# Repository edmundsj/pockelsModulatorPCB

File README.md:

# pockelsModulatorPCB
Printed Circuit Board (PCB) for pockels modulator chip

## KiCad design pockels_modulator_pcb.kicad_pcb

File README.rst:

.. _pockels_modulator_pcb:

[PCBPOCK1] Pockels Modulator PCB
=================================

Printed Circuit Board (PCB) for pockels modulator chip

Fixed in Version 2
-------------------
#. [FIXED v3] Add thermal vias on the ground plane of the device so that we can easily transfer heat to the device
#. [FIXED v3] Add thermal pads adjacent 
#. [FIXED v3] Flipped silkscreen to have proper orientation
#. The temp-PCB connector can be reduced to one that has 4 pins, should be made smaller

Fixed in Version 3

Debugging thermal PCB
----------------------
- For some reason, it looks like after soldering my temperature sensing IC, it consumes huge amounts of current (>500mA on startup), indicating it is connected improperly or has an internal short. I didn't go above 550F when soldering it, and did relatively quick reflow soldering followed by brief rework with the soldering iron. VDD and GND aren't shorted when I probe the board itself, so it's actually the chip using the current.
- The package itself and the silkscreen appear to be inverted. The footprint is wrong. GND is connected to VDD and VDD is connected to GND. This doesn't appear to be an error on the package, but perhaps an error in KiCad?
- Make sure to apply VDD and THEN GND, it appears I damaged the temperature IC by applying GND to VDD and vice versa. Now it's fluctuating +/- 0.2 degrees pretty wildly. Everything is working, though. Can't guarantee specs of the current temp PCB. Going to make another one. Let's make the last 3.
- For some reason all the PCBs have fluctuating temperatures - much more than the breakout board. They appear to be measuring room temperature as room temperature (within about 1C). Perhaps I should do some averaging, or perhaps the dev boards I got were pre-programmed to do that on chip? DAMN. Even out to 75V the film STILL hasn't broken down. The first device I swept from 0 to 50V and then 0 to 75V and now I'm going to 100V. I think I may have overrun the keithley's buffer asking it to measure 300 data points. Looks like it has a max buffer size of ~250 measurements.
- I applied a positive voltage directly to the ITO mesa.

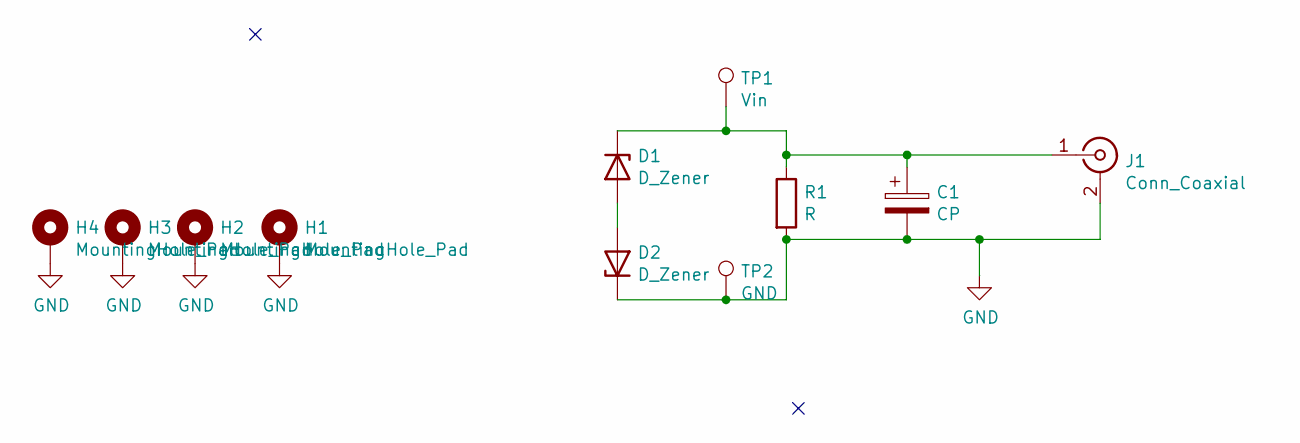
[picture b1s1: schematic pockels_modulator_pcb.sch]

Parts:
C1: CP; pockels_chip_10mm_thermal
D1, D2: D_Zener; C_0805_2012Metric_Pad1.15x1.40mm_HandSolder
H1, H2, H3, H4: MountingHole_Pad; m3_mounting_hole
J1: Conn_Coaxial; CON-SMA-EDGE-S
R1: R; C_0805_2012Metric_Pad1.15x1.40mm_HandSolder
TP1: Vin; TestPoint_Keystone_5000-5004_Miniature
TP2: GND; TestPoint_Keystone_5000-5004_Miniature

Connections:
GND: C1.2, D2.1 (K), H1.1, H2.1, H3.1, H4.1, J1.2 (Ext), R1.2, TP2.1
unnamed: C1.1, D1.1 (K), J1.1 (In), R1.1, TP1.1
unnamed: D1.2 (A), D2.2 (A)

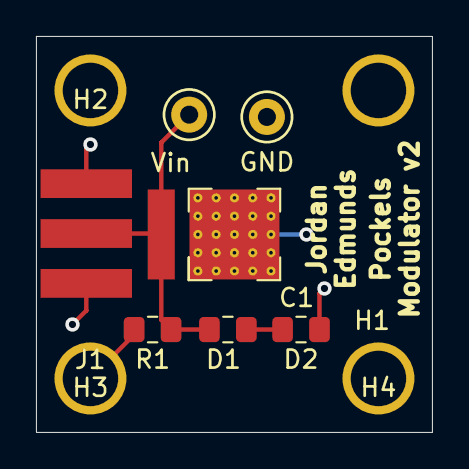
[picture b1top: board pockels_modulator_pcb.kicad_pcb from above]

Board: 2 copper layers, 22.0 x 22.0 mm, 11 parts (0 on the bottom side), 3 nets.

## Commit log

2020-10-05 added version 1 of pockels modulator PCB
2021-01-05 revised pockels modulator PCB to include thermal vias, chip for thermal sensing, SMD connector
2021-03-02 tweaked PCB in a manner I don't remember how. This is why you commit immediately after working.
2022-03-24 updated for new 5mm chips to version 3
